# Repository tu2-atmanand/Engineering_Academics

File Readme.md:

# Engineering Academics

This repository contains the Experiments i performed during my B.Tech in Electronics and Telecommunication Engineering course in few of the courses.
Following are the courses and their corresponding experiments

## ADC - Anolog and Digital Communication (SEM - 5)

Exp 1 :
Exp 2 :
Exp 3 :
Exp 4 :
Exp 5 :
Exp 6 :
Exp 7 :
Exp 8 :
Exp 9 :
Exp 10 :
Exp 11 :
Exp 12 :

## VLSI Technology and Design Lab (SEM - 6)

Exp 1 :
Exp 2 :
Exp 3 :
Exp 4 :
Exp 5 :
Exp 6 :
Exp 7 :
Exp 8 :
Exp 9 :
Exp 10 :

## ESD - Electronic System and Design (SEM - 6)

Exp 1 :
Exp 2 :
Exp 3 :
Exp 4 :
Exp 5 :
Exp 6 :
Exp 7 :
Exp 8 :
Exp 9 :

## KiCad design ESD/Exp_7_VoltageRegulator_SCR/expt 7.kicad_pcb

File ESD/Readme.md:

# ESD - Electronic System and Design (SEM - 6)

## Exp 1 : Center-Tapped Full Wave Rectifier

## Exp 2 : Voltage Regulator

## Exp 3 : Amplifier

## Exp 4 : 5V Regulated Power Supply

## Exp 5 : DIY PCB Making of Exp 1

## Exp 6 : DIY PCB Making of Exp 2

## Exp 7 : Voltage Regulator Using SCR

## Exp 8 : Fire Alarm Mini Project

## Exp 9 : Audio Amplifier

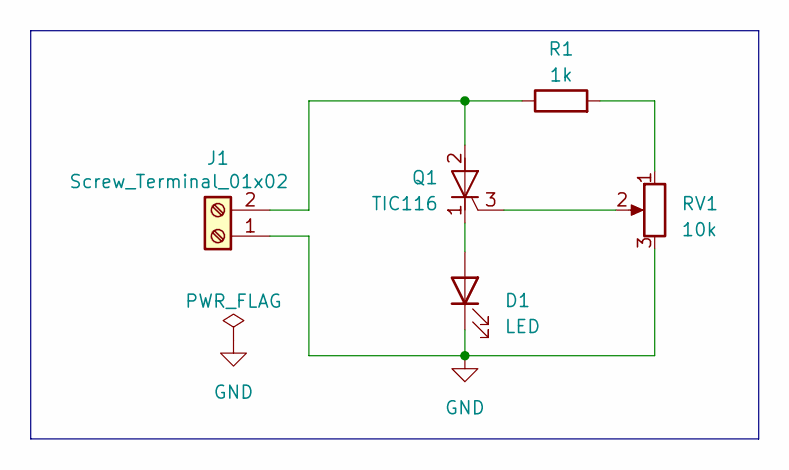
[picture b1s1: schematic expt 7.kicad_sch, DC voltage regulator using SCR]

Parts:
D1: LED; LED_D3.0mm
J1: Screw_Terminal_01x02; TerminalBlock_Phoenix_MKDS-1,5-2-5.08_1x02_P5.08mm_Horizont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
Q1: TIC116; TO-220-3_Vertical
R1: 1k; R_Axial_DIN0414_L11.9mm_D4.5mm_P15.24mm_Horizontal
RV1: 10k; Potentiometer_Bourns_3339P_Vertical_HandSoldering

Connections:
GND: D1.1 (K), J1.1, RV1.3
unnamed: D1.2 (A), Q1.1 (K)
unnamed: J1.2, Q1.2 (A), R1.1
unnamed: Q1.3 (G), RV1.2
unnamed: R1.2, RV1.1

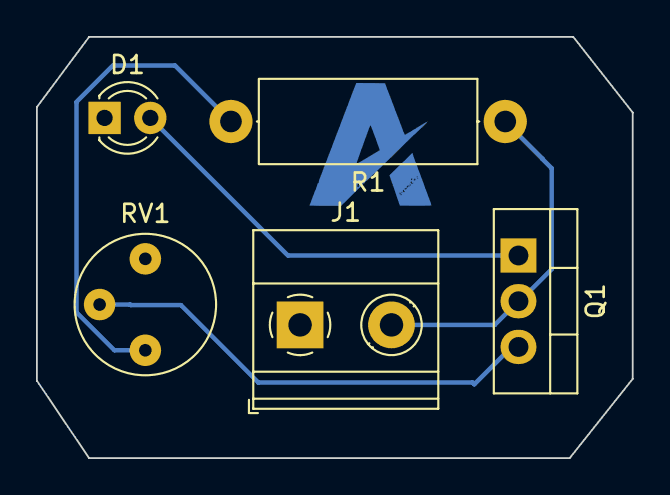
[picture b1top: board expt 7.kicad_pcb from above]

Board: 2 copper layers, 33.1 x 23.4 mm, 5 parts (0 on the bottom side), 5 nets.

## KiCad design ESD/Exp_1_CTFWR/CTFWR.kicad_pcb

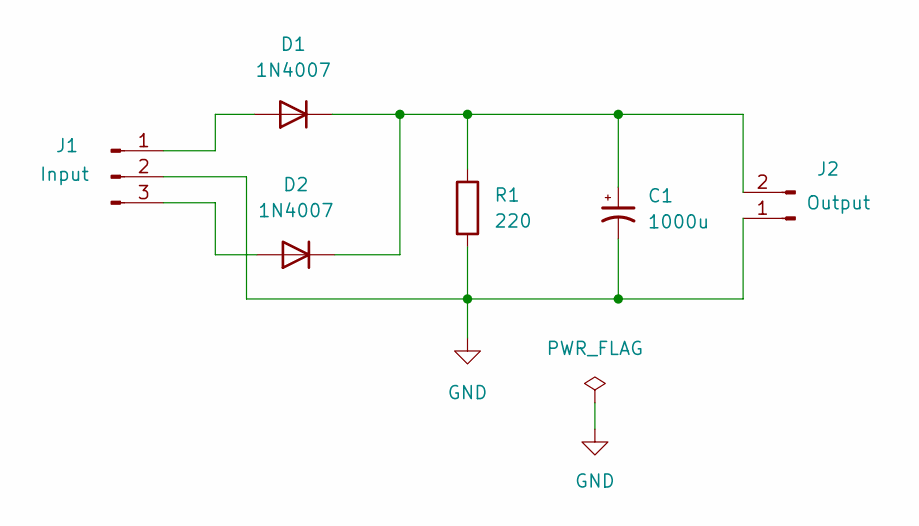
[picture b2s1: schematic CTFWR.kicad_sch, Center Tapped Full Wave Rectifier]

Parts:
C1: 1000u; CP_Radial_D10.0mm_P2.50mm_P5.00mm
D1, D2: 1N4007; D_DO-41_SOD81_P10.16mm_Horizontal
J1: Input; PinHeader_1x03_P2.54mm_Vertical
J2: Output; PinHeader_1x02_P2.54mm_Vertical
R1: 220; R_Axial_DIN0414_L11.9mm_D4.5mm_P20.32mm_Horizontal

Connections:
GND: C1.2, J1.2, J2.1, R1.2
unnamed: C1.1, D1.1 (K), D2.1 (K), J2.2, R1.1
unnamed: D1.2 (A), J1.1
unnamed: D2.2 (A), J1.3

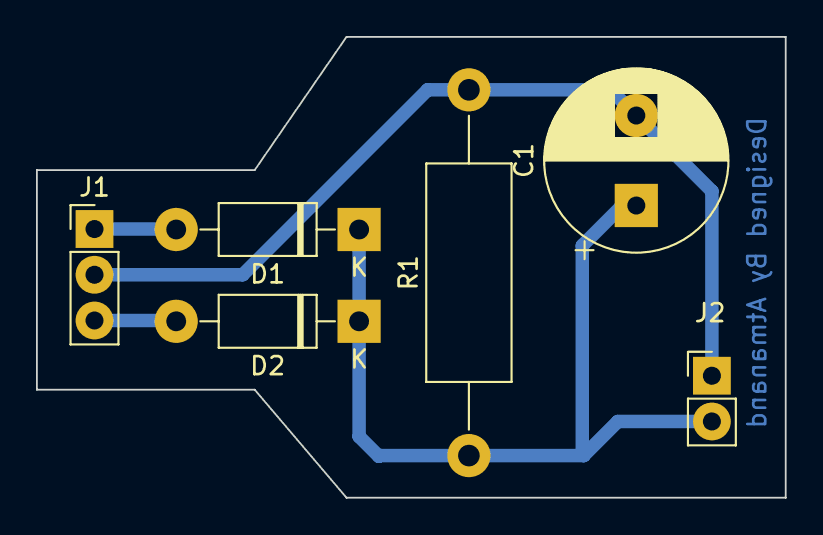
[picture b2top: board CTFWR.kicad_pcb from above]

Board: 2 copper layers, 41.6 x 25.6 mm, 6 parts (0 on the bottom side), 4 nets.

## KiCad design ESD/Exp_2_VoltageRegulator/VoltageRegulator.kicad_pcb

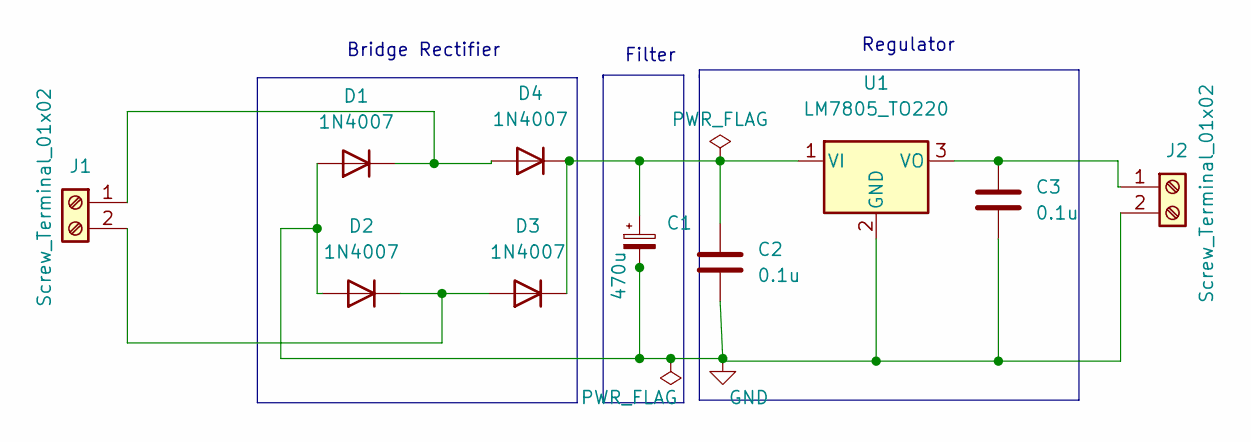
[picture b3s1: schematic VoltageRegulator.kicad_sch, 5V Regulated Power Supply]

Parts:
C1: 470u; CP_Radial_D8.0mm_P3.80mm
C2, C3: 0.1u; C_Disc_D4.7mm_W2.5mm_P5.00mm
D1, D2, D3, D4: 1N4007; D_DO-41_SOD81_P10.16mm_Horizontal
J1, J2: Screw_Terminal_01x02; TerminalBlock_Phoenix_MKDS-1,5-2_1x02_P5.00mm_Horizontal
U1: LM7805_TO220; TO-220-3_Vertical

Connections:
GND: C1.2, C2.2, C3.2, D1.2 (A), D2.2 (A), J2.2, U1.2 (GND)
unnamed: C1.1, C2.1, D3.1 (K), D4.1 (K), U1.1 (VI)
unnamed: C3.1, J2.1, U1.3 (VO)
unnamed: D1.1 (K), D4.2 (A), J1.1
unnamed: D2.1 (K), D3.2 (A), J1.2

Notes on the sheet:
Regulator
Filter
Bridge Rectifier

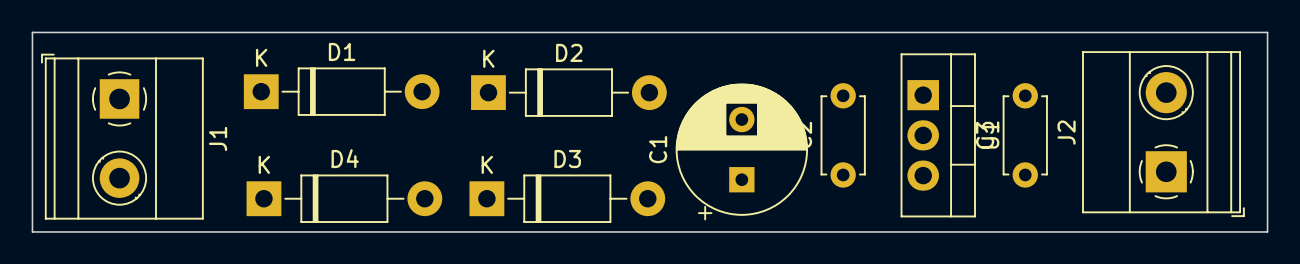
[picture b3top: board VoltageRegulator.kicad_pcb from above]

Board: 2 copper layers, 78.0 x 12.6 mm, 10 parts (0 on the bottom side), 5 nets.

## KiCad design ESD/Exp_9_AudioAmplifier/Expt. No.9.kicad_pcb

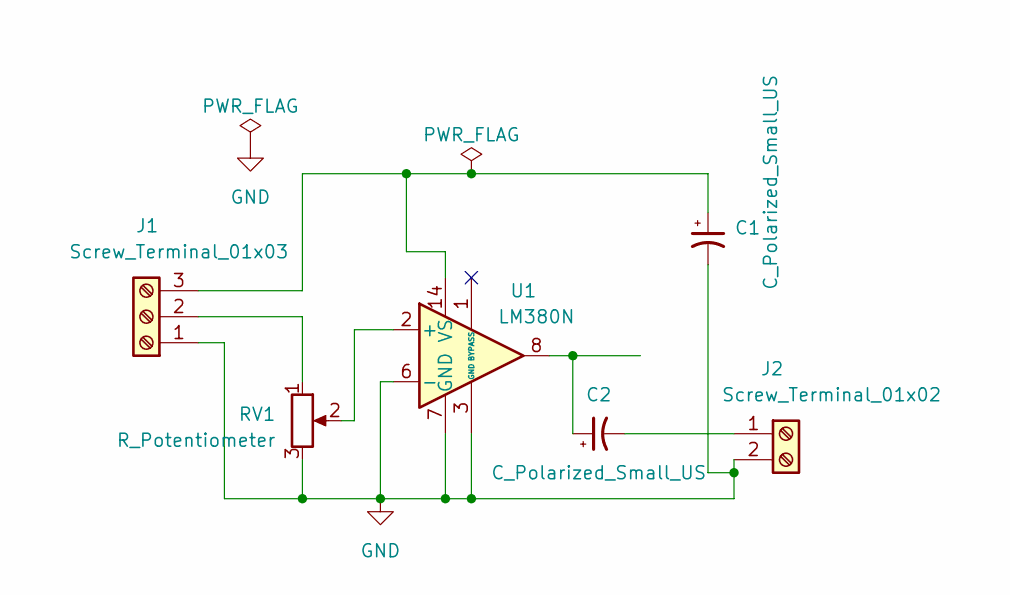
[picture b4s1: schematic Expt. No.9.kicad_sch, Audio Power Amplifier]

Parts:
C1, C2: C_Polarized_Small_US; CP_Radial_D8.0mm_P3.50mm
J1: Screw_Terminal_01x03; TerminalBlock_Phoenix_MKDS-3-3-5.08_1x03_P5.08mm_Horizontal
J2: Screw_Terminal_01x02; TerminalBlock_Phoenix_MKDS-1,5-2-5.08_1x02_P5.08mm_Horizont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
RV1: R_Potentiometer; Potentiometer_Runtron_RM-065_Vertical
U1: LM380N; DIP-14_W7.62mm

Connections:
GND: C1.2, J1.1, J2.2, RV1.3, U1.3 (GND), U1.4 (GND), U1.5 (GND), U1.6 (-), U1.7 (GND), U1.10 (GND), U1.11 (GND), U1.12 (GND)
unnamed: C2.1, U1.8
unnamed: J1.2, RV1.1
unnamed: C1.1, J1.3, U1.14 (VS)
unnamed: C2.2, J2.1
unnamed: RV1.2, U1.2 (+)

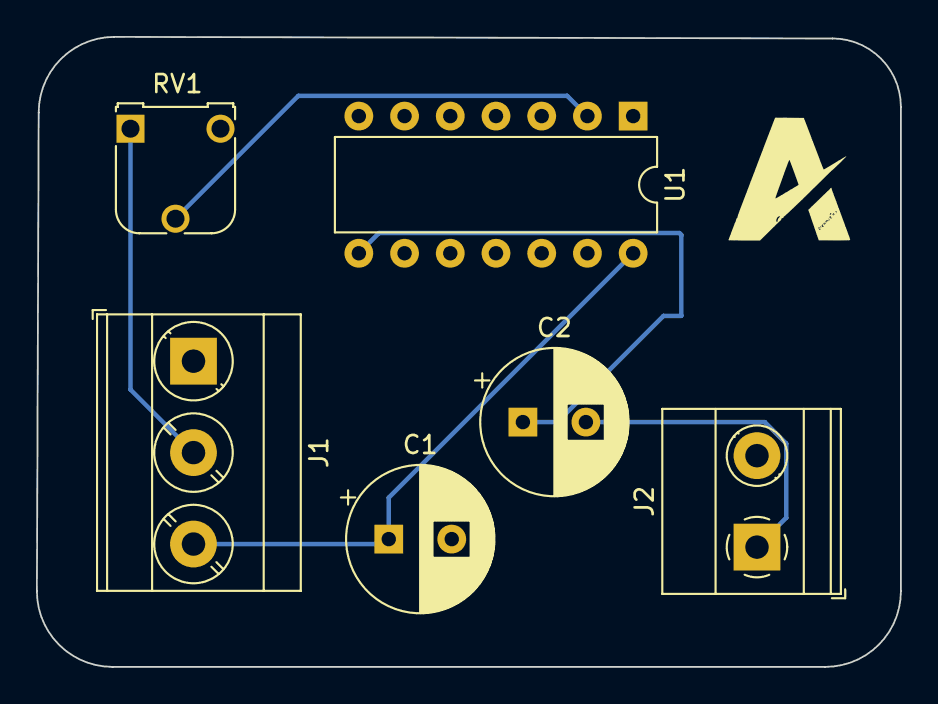
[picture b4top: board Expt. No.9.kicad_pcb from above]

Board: 2 copper layers, 48.0 x 35.0 mm, 6 parts (0 on the bottom side), 6 nets.

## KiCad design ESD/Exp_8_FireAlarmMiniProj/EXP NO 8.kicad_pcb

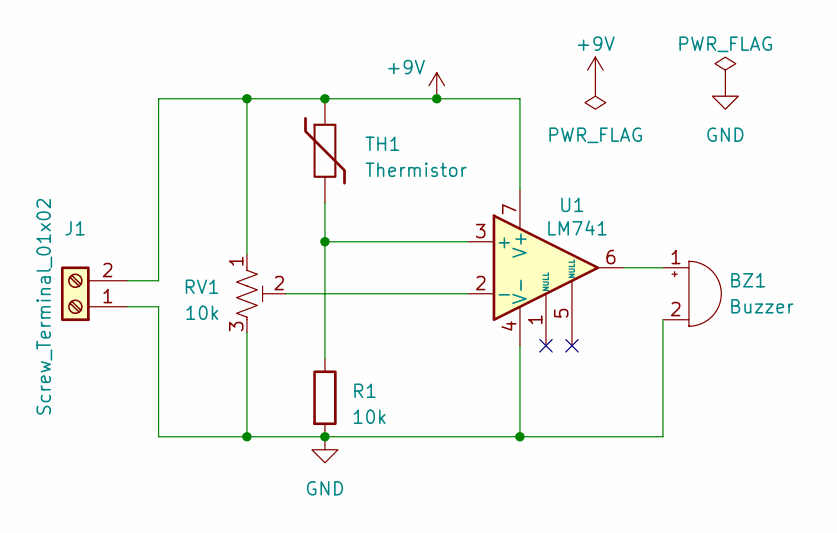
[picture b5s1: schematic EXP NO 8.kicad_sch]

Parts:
BZ1: Buzzer; Buzzer_12x9.5RM7.6
J1: Screw_Terminal_01x02; TerminalBlock_Phoenix_MKDS-1,5-2-5.08_1x02_P5.08mm_Horizont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
R1: 10k; R_Axial_DIN0204_L3.6mm_D1.6mm_P5.08mm_Horizontal
RV1: 10k; Potentiometer_Runtron_RM-063_Horizontal
TH1: Thermistor; THERM_NXRT15WB473FA1B020
U1: LM741; DIP-8_W7.62mm

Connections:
+9V: J1.2, RV1.1, TH1.1, U1.7 (V+)
GND: BZ1.2 (+), J1.1, R1.2, RV1.3, U1.4 (V-)
unnamed: BZ1.1 (-), U1.6
unnamed: R1.1, TH1.2, U1.3 (+)
unnamed: RV1.2, U1.2 (-)

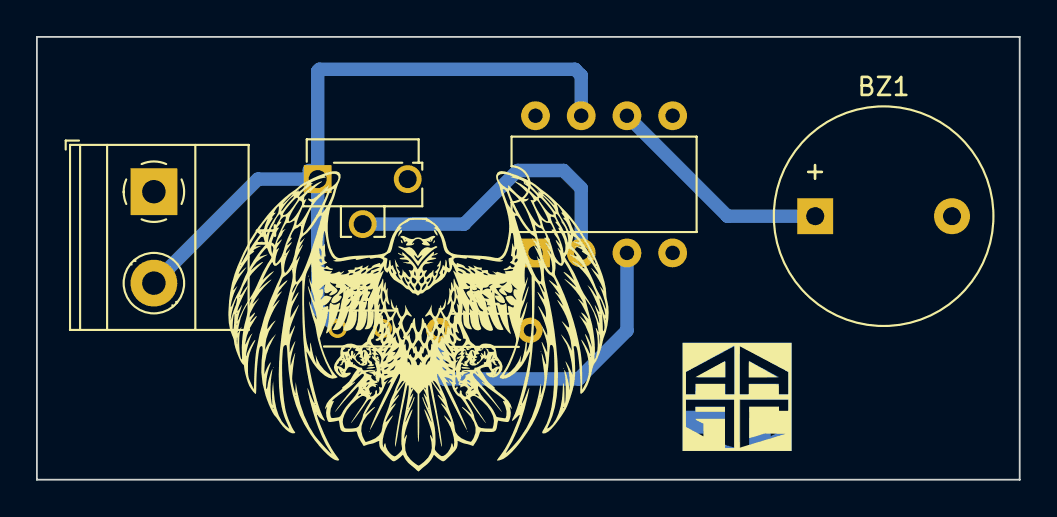
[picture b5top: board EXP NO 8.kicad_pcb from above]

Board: 2 copper layers, 54.6 x 24.6 mm, 6 parts (0 on the bottom side), 5 nets.

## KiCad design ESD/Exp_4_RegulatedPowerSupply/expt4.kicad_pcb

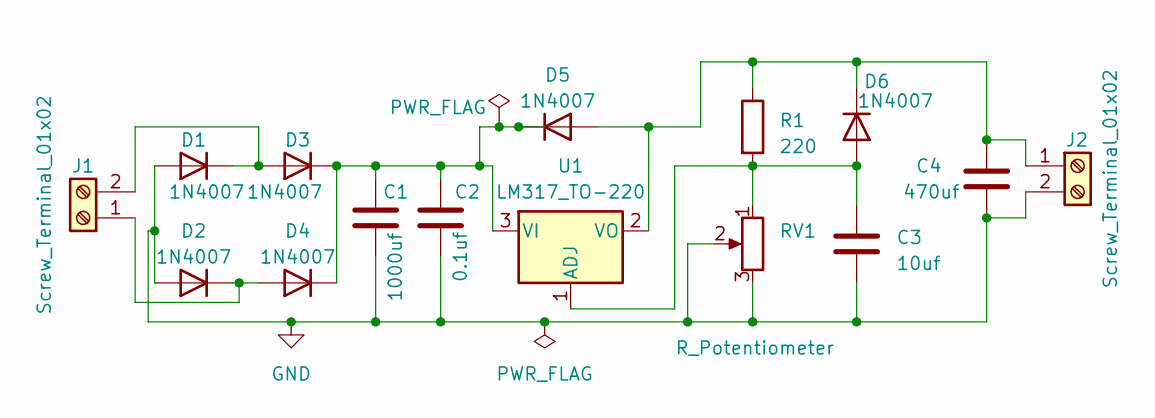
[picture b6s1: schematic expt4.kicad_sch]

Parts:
C1: 1000uf; C_Radial_D12.5mm_H20.0mm_P5.00mm
C2: 0.1uf; C_Disc_D4.7mm_W2.5mm_P5.00mm
C3: 10uf; C_Radial_D5.0mm_H11.0mm_P2.00mm
C4: 470uf; C_Radial_D10.0mm_H12.5mm_P5.00mm
D1, D2, D3, D4, D5, D6: 1N4007; D_DO-41_SOD81_P10.16mm_Horizontal
J1, J2: Screw_Terminal_01x02; TerminalBlock_Phoenix_MKDS-1,5-2-5.08_1x02_P5.08mm_Horizont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
R1: 220; R_Axial_DIN0207_L6.3mm_D2.5mm_P7.62mm_Horizontal
RV1: R_Potentiometer; Potentiometer_Runtron_RM-065_Vertical
U1: LM317_TO-220; TO-220-3_Vertical

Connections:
GND: C1.2, C2.2, C3.2, C4.2, D1.2 (A), D2.2 (A), J2.2, RV1.2, RV1.3
unnamed: D1.1 (K), D3.2 (A), J1.2
unnamed: D2.1 (K), D4.2 (A), J1.1
unnamed: C1.1, C2.1, D3.1 (K), D4.1 (K), D5.1 (K), U1.3 (VI)
unnamed: C4.1, D5.2 (A), D6.1 (K), J2.1, R1.1, U1.2 (VO)
unnamed: C3.1, D6.2 (A), R1.2, RV1.1, U1.1 (ADJ)

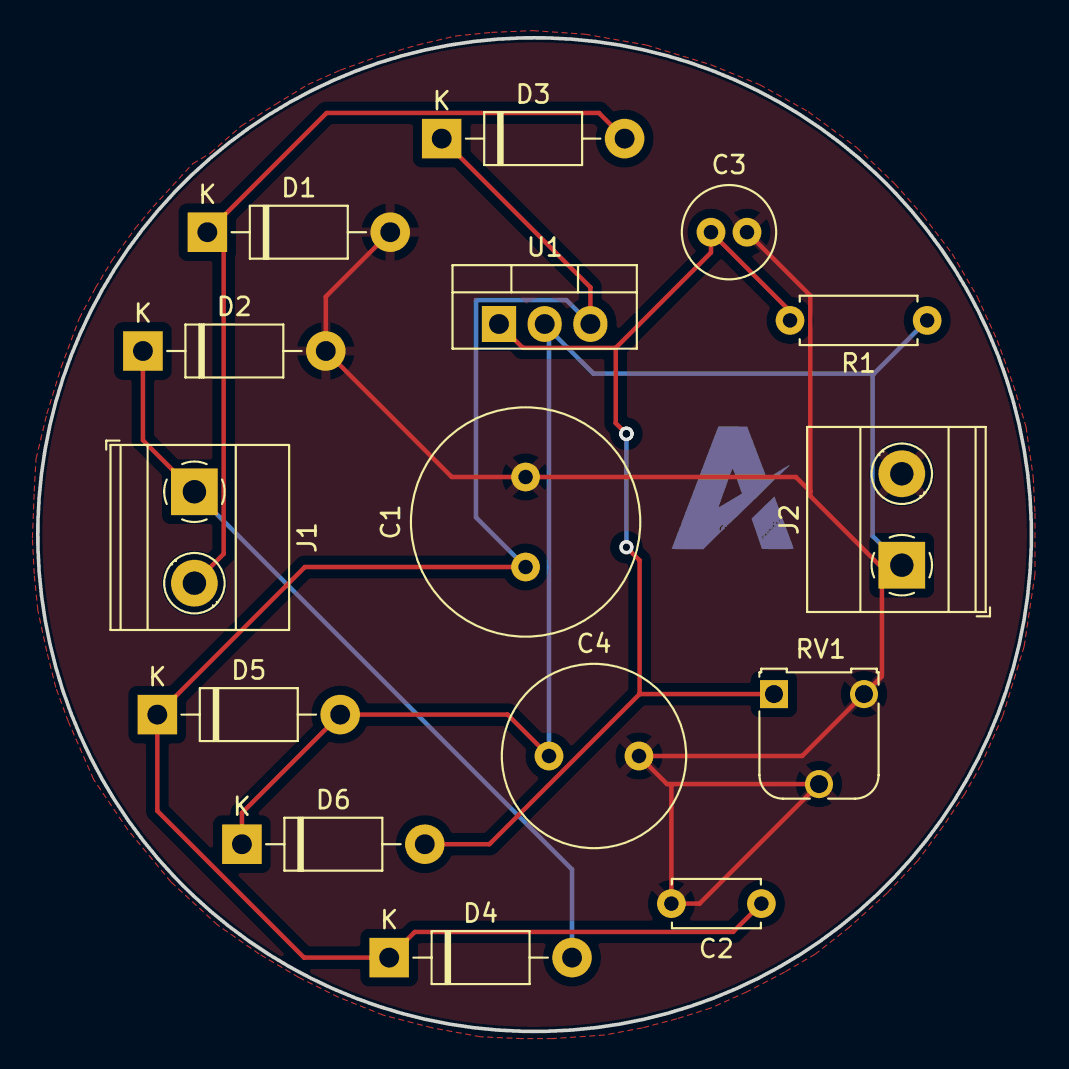
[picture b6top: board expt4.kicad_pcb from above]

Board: 2 copper layers, 55.2 x 55.2 mm, 15 parts (0 on the bottom side), 6 nets.

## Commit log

2023-03-10 Added Workshop Project
2023-03-10 Added readme in workshop
2023-03-10 Added ADC Project
2023-03-10 Added ESD Project
2023-03-11 Added Notes dir and update readme
2023-03-11 Added gitignore in ESD
2023-03-11 Added gitignore in main dir
2023-03-13 Added Readme
2023-03-13 Removed the pico project
2023-03-22 Added Main readme
2023-03-30 Added EXP1 in VLSI
2023-03-30 Added EXP2 in VLSI
2023-03-30 Added EXP3 in VLSI
2023-04-06 Added final EXP 2
2023-06-04 Updated all EXP3 file VLSI Lab
2023-06-04 Added EXP4 in VLSI lab
2023-06-04 Added EXP5 in VLSI lab
2023-06-04 Added EXP6 in VLSI lab
2023-06-04 Added EXP7 in VLSI lab
2023-06-04 Updated Verilog Workshop Folder
2023-07-29 Add second Exp in ESD
2023-07-29 Update Exp 1 in ESD
2023-07-29 Add third Exp in ESD
2023-07-29 Add forth Exp in ESD
2023-07-29 update forth Exp in ESD
2023-07-29 Add seventh Exp in ESD
2023-07-29 Update seventh Exp in ESD
2023-07-29 Add Eighth Exp in ESD
2023-07-29 Update Eighth Exp in ESD
2023-07-29 Add Ninth Exp in ESD
2023-07-29 Add eighth Exp in VLSI
2023-07-29 Add ninth Exp in VLSI
2023-07-29 Add tenth Exp in VLSI
2023-07-29 Add Readme in all folders
